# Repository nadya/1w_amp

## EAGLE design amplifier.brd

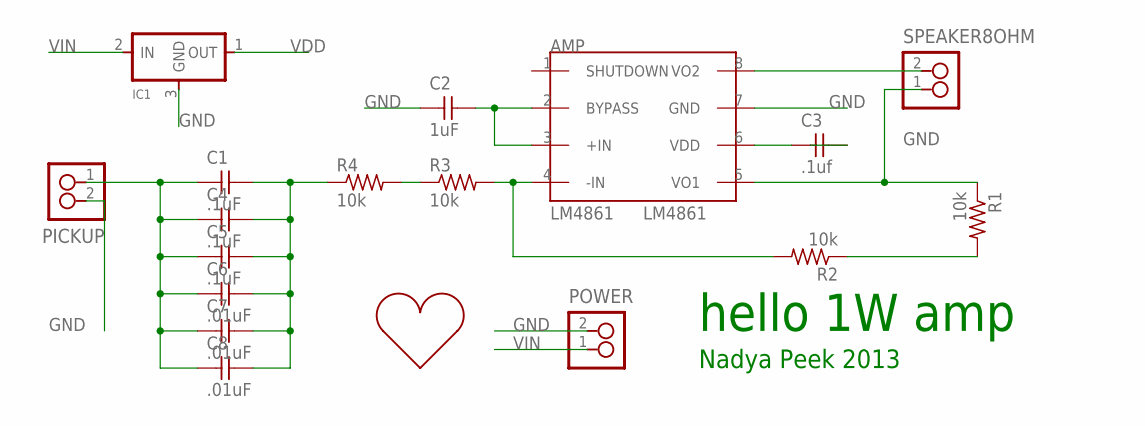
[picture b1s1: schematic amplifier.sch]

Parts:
AMP: LM4861; SOIC8
C1, C4, C5: .1uF; 1206
C2: 1uF; 1206
C3: .1uf; 1206
C6, C7, C8: .01uF; 1206
IC1: REGULATORSOT23; SOT23
PICKUP: 2_PIN_HEADERSCREW; SCREW_2
POWER: 2_PIN_HEADERSCREW; SCREW_2
R1, R2, R3, R4: 10k; 1206
SPEAKER8OHM: 2_PIN_HEADERSCREW; SCREW_2
U$2: SMALLHEARTSMALL; SMALLERHEART

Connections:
GND: AMP.7 (GND), C2.1, C3.2, IC1.3 (GND), PICKUP.2, POWER.2
unnamed: AMP.4 (-IN), R2.2, R3.2
unnamed: R3.1, R4.2
unnamed: AMP.2 (BYPASS), AMP.3 (+IN), C2.2
unnamed: AMP.5 (VO1), R1.1, SPEAKER8OHM.1
unnamed: R1.2, R2.1
unnamed: C1.2, C4.2, C5.2, C6.2, C7.2, C8.2, R4.1
unnamed: C1.1, C4.1, C5.1, C6.1, C7.1, C8.1, PICKUP.1
SPEAKER: AMP.8 (VO2), SPEAKER8OHM.2
VDD: AMP.6 (VDD), C3.1, IC1.1 (OUT)
VIN: IC1.2 (IN), POWER.1

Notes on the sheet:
hello 1W amp
Nadya Peek 2013

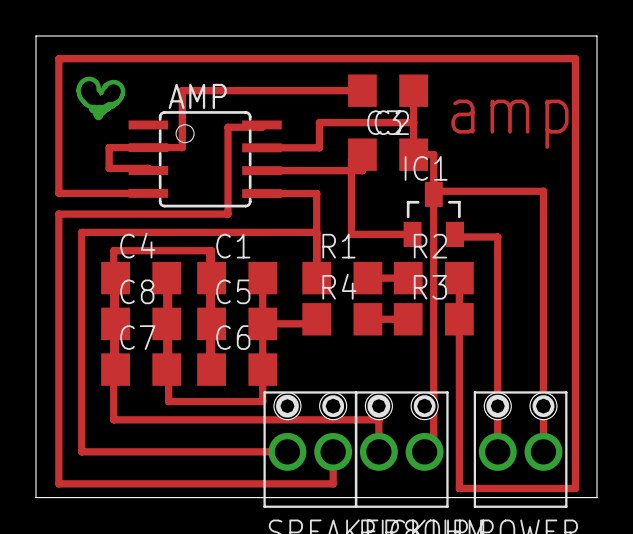
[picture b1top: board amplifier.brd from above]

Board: 2 copper layers, 31.2 x 25.6 mm, 18 parts (0 on the bottom side), 11 nets.

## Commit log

2013-09-04 added board files and schematic
2013-09-04 added a picture
